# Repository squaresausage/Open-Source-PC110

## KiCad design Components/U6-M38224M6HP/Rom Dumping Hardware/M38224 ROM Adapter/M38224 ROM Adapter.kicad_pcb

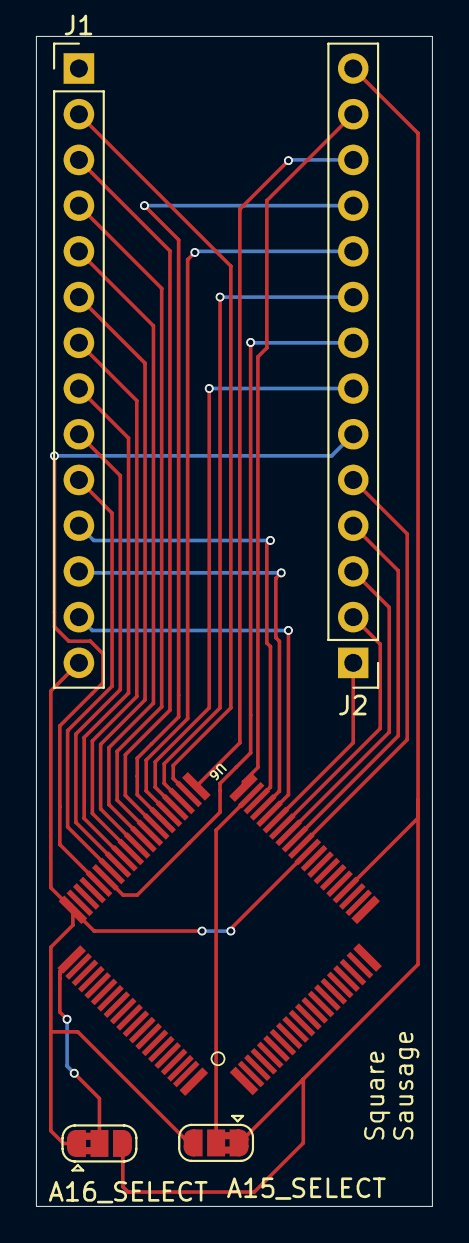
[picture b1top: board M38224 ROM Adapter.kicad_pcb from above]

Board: 2 copper layers, 22.0 x 65.0 mm, 5 parts (0 on the bottom side), 29 nets.

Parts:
J1, J2: Conn_01x14; PinHeader_1x14_P2.54mm_Vertical
JP1: A15_SELECT; SolderJumper-3_P1.3mm_Bridged2Bar12_RoundedPad1.0x1.5mm
JP2: A16_SELECT; SolderJumper-3_P1.3mm_Bridged2Bar12_RoundedPad1.0x1.5mm
U6: M38223E4HP; QFN-80

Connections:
#CE: J2.6, U6.56 (P36)
#OE: J2.8, U6.55 (P37)
A0: J1.10, U6.54 (SEG00)
A1: J1.9, U6.53 (SEG01)
A2: J1.8, U6.52 (P02)
A3: J1.7, U6.51 (P03)
A4: J1.6, U6.50 (P04)
A5: J1.5, U6.49 (P05)
A6: J1.4, U6.48 (P06)
A7: J1.3, U6.47 (SEG07)
A8: J2.11, U6.46 (P10)
A9: J2.10, U6.45 (P11)
A10: J2.7, U6.44 (P12)
A11: J2.9, U6.43 (P13)
A12: J1.2, U6.42 (P14)
A13: J2.12, U6.41 (P15)
A14: J2.13, U6.40 (P16)
A15: JP1.2 (C), U6.39 (P17)
A16: JP2.2 (C), U6.61 (SEG9)
D0: J1.11, U6.38 (P20)
D1: J1.12, U6.37 (P21)
D2: J1.13, U6.36 (P22)
D3: J2.1, U6.35 (P23)
D4: J2.2, U6.34 (P24)
D5: J2.3, U6.33 (P25)
D6: J2.4, U6.32 (P26)
D7: J2.5, U6.31 (P27)
GND: J1.14, JP1.3 (B), JP2.1 (A), U6.30 (GND), U6.60 (SEG10)
VCC: J2.14, JP1.1 (A), JP2.3 (B), U6.24 (P40)

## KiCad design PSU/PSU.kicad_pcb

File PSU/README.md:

## Here is the PCB Layout for the PSU board

Layer Stack-up

| Index | Layer name | Description  |
| ----- | ---------- | ------------ |
| 1     | FC         | Top          |
| 2     | IC         | Signal       |
| 3     | IP         | Ground       |
| 4     | BC         | Bottom       |

Here is a render of FC, IC, IP and BC:

Here are 3D models of the PSU board:

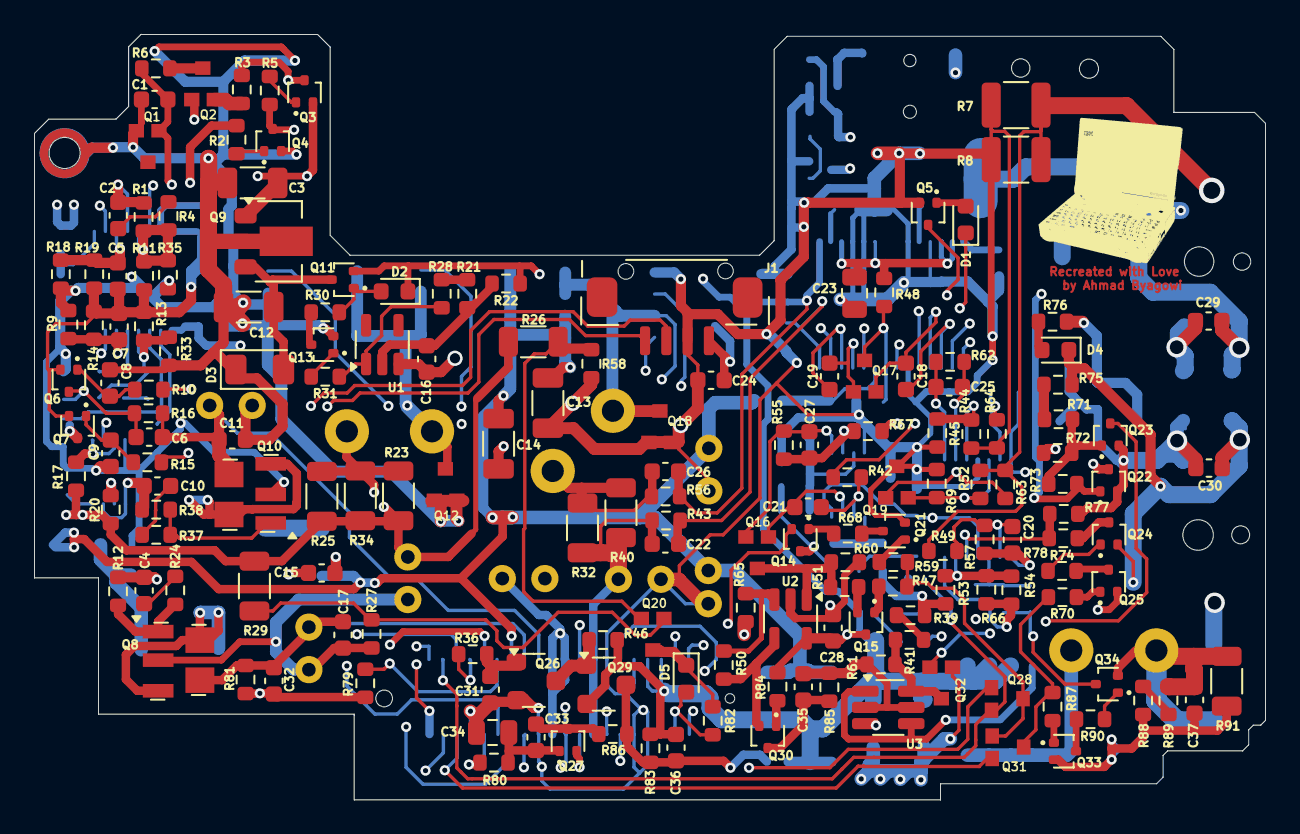
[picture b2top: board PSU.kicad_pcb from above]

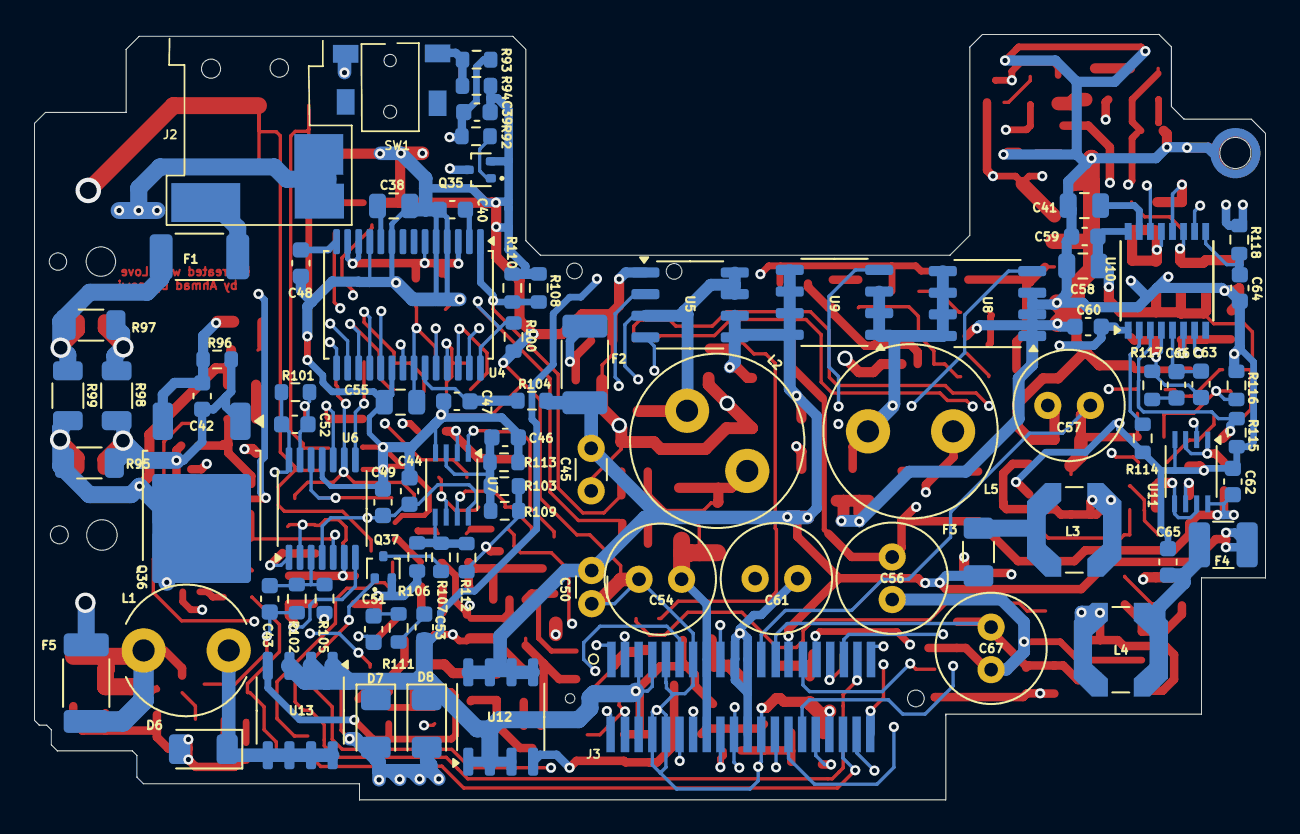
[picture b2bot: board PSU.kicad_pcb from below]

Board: 4 copper layers, 72.3 x 45.0 mm, 257 parts (86 on the bottom side), 155 nets.

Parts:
C1, C5, C7, C16, C24, C28, C36, C46, C47, C59: 150nF; C_0603_1608Metric
C2: 4.7nF; C_0603_1608Metric
C3: 5.2uF; C_1206_3216Metric
C4: 2.5nF; C_0603_1608Metric
C6, C20: 100pF; C_0603_1608Metric
C8, C33: 24nF; C_0603_1608Metric
C9, C17, C22, C26, C29, C30, C32, C39, C40, C48: 10nF; C_0603_1608Metric
C10: 3.6nF; C_0603_1608Metric
C11, C15, C37, C44, C49: 180nF; C_0603_1608Metric
C12: 1.2uF; C_1206_3216Metric
C13, C14: 1.5uF; C_1206_3216Metric
C18, C42, C51, C53, C64: 120nF; C_0603_1608Metric
C19: 18nF; C_0603_1608Metric
C21: 12nF; C_0603_1608Metric
C23, C34, C38, C41, C55, C58: 1.5uF; C_0805_2012Metric
C25, C27, C31, C35, C66: 1.2nF; C_0603_1608Metric
C43: 10pF; C_0603_1608Metric
C45: 33uF 20V; C_Disc_D3.0mm_W1.6mm_P2.50mm
C50: 56uF 25V EC; EC
C52, C60: 1nF; C_0603_1608Metric
C54, C61: 47uF 6.3v; C_Radial_D6.3mm_H11.0mm_P2.50mm
C56: 47uF 6.3V; C_Radial_D6.3mm_H11.0mm_P2.50mm
C57: 15uF 16V; C_Radial_D6.3mm_H11.0mm_P2.50mm
C62, C65: 100nF; C_0603_1608Metric
C63: 5.1nF; C_0603_1608Metric
C67: 18uF 50V; C_Radial_D6.3mm_H11.0mm_P2.50mm
D1: 8-2; D_0603_1608Metric
D2: 5-9; D_0603_1608Metric
D3, D6: DNP; D_1206_3216Metric
D4: 18; D_0603_1608Metric
D5: 3^9; D_0603_1608Metric
D7, D8: s.3 4F; D_1206_3216Metric
F1, F5: 2.5A; Fuse_2010_5025Metric
F2: 830mA; Fuse_2010_5025Metric
F3: 15; Fuse_1206_3216Metric
F4: 10; Fuse_1210_3225Metric
J1: Backllight_Connector
J2: PSU_Jack
J3: PSU_Connector_Receptor
L1: 10uH; L_Radial_D7.5mm_P5.00mm_Fastron_07P
L2, L5: 10uH; L_Radial_D10.0mm_P5.00mm_Fastron_07M
L3: 68uH; L_Coilcraft_LPS5030
L4: 470uH; L_Coilcraft_LPS5030
Q1: R4C; 3D
Q2, Q32: K; 3D
Q3, Q6, Q7, Q11, Q14, Q24, Q34: 6LS; SOT-416
Q4, Q13, Q15, Q33, Q37: 8LR; SOT-416
Q5, Q21, Q22, Q23, Q27, Q30, Q35: 8C; SOT-416
Q8: 303 5H; SOT-powerT
Q9: KD 3.E; SOT-89-3
Q10: 103 5G; SOT-powerT
Q12, Q18: Q; 3D
Q16, Q17, Q19: M2P; 3D
Q20, Q28, Q31: W6; 3D
Q25: 8LB; SOT-416
Q26: G16; SOT-23-PC110
Q29: H15; SOT-23-PC110
Q36: 3P4J; TO-252-2
R1, R50, R66, R82, R108: DNP; R_0603_1608Metric
R2, R10, R21, R31, R70, R74, R83, R87, R90: 470k; R_0603_1608Metric
R3, R36, R65, R71, R72, R75, R76, R93: 1k; R_0603_1608Metric
R4, R11, R13, R17, R19, R20, R30, R33, R35, R44, R52, R61, R63, R64, R85, R86, R103, R114, R117: 10k; R_0603_1608Metric
R5, R15, R22, R54, R57, R59, R77, R80, R84, R92, R105: 100k; R_0603_1608Metric
R6, R38: 470; R_0603_1608Metric
R7, R8: 0.1; R_1210_3225Metric
R9, R18, R112, R113: 20k; R_0603_1608Metric
R12: 2.2k; R_0603_1608Metric
R14: 12k; R_0603_1608Metric
R16: 130k; R_0603_1608Metric
R23, R25, R32, R34: 0.1; R_1206_3216Metric
R24: 220; R_0603_1608Metric
R26: 103 (RT1); R_1206_3216Metric
R27, R39, R41, R51, R58, R60, R106: 4.7k; R_0603_1608Metric
R28: 0; R_0603_1608Metric
R29: 103 (RT2); R_1206_3216Metric
R37: 120; R_0603_1608Metric
R40: 0.22; R_1206_3216Metric
R42, R47, R67, R68, R73, R79, R94: 47k; R_0603_1608Metric
R43, R56: 300; R_0603_1608Metric
R45, R62, R69, R81, R101, R109: 200k; R_0603_1608Metric
R46, R55, R88, R89: 1M; R_0603_1608Metric
R48, R104, R118: 100; R_0603_1608Metric
R49, R53, R78, R102: 300k; R_0603_1608Metric
R91, R95, R97: DNP; R_1206_3216Metric
R96: 1.8k; R_0603_1608Metric
R98, R99: 0; R_1206_3216Metric
R100, R110: 7.5k; R_0603_1608Metric
R107: 2k; R_0603_1608Metric
R111: 33; R_0603_1608Metric
R115: 11K; R_0603_1608Metric
R116: 15k; R_0603_1608Metric
SW1: PSU-SW1
U1: D9D; SOT-23-5
U2: TA; SOT-23-5
U3: 6.5 5F; SOT-23-6_Handsoldering
U4: MAX786CAI; TSSOP-28_6.1x9.7mm_P0.65mm
U5: K2337; SOP-8_3.9x4.9mm_P1.27mm
U6: 7064; TSSOP-14_4.4x5mm_P0.65mm
U7: 5W01; SSOP-8-PSU
U8, U9: 2556; SOP-8_3.9x4.9mm_P1.27mm
U10: 9742; SSOP-16_4.4x5.2mm_P0.65mm
U11: 7W14; SSOP-8-PSU
U12, U13: J421; SOP-8_3.9x4.9mm_P1.27mm

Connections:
BATT_POS: R7.2, R8.2, R49.1, R52.2, R63.2
C1_1: C2.1, R4.1
C1_2: C2.2, R1.1, U10.12
C6_1: C4.1, R24.2
C6_2: C4.2, R12.2, U11.2
C8_1: C7.1, R9.2, R14.2, U10.6
C14_2: C12.2, D3.2, Q9.3, Q11.3
C31_1: C33.1, Q27.3, R86.2
C32_1: C33.2, C34.1, Q27.1, R80.1
C33_1: C31.1, Q26.1, R36.1
C35_2: C36.2, Q29.3, R83.2, R86.1, U12.4
C36_1: C35.1, R61.1, R85.2, U3.2, U3.5
C36_2: C35.2, Q30.3, R85.1
D1_2: D1.2, Q5.1
D2_3_PC110: J3.26, Q23.3
D18_2_3_PC110: J1.1, J3.40
D28_1_PC110: C6.2, C11.1, C57.1, J3.12, Q10.4, R16.2
F3_1: F3.1, L3.1
F65_ENAVEE_PC110: J3.35, R15.1
GND: C1.1, C3.1, C8.2, C9.1, C11.2, C12.1, C13.2, C14.2, C15.2, C16.2, C17.1, C23.1, C24.1, C28.1, C30.1, C31.2, C34.2, C37.1, C38.2, C39.2, C40.1, C41.1, C42.2, C44.2, C45.1, C46.2, C47.1, C48.2, C49.2, C50.1, C51.1, C54.2, C55.1, C56.1, C57.2, C58.1, C59.2, C60.1, C61.2, C62.1, C64.2, C65.2, C67.1, D3.1, D6.2, J1.3, J3.5, J3.7, J3.9, J3.24, J3.25, J3.29, J3.32, J3.37, Q1.1, Q4.2, Q5.2, Q8.2, Q9.2, Q10.2, Q12.1, Q12.3, Q13.2, Q18.1, Q18.3, Q19.2, Q21.2, Q22.2, Q23.2, Q25.2, Q26.2, Q27.2, Q33.2, Q35.2, Q36.1, Q37.2, R7.1, R8.1, R9.1, R18.2, R27.1, R33.2, R35.2, R39.2, R44.1, R45.1, R53.1, R58.1, R60.2, R64.1, R69.2, R72.1, R77.2, R88.1, R91.1, R94.2, R95.2, R96.2, R98.2, R100.2, R105.2, R106.2, R108.1, R110.1, R113.2, R114.2, R115.2, R116.1, U1.3, U2.2, U3.3, U4.4, U4.5, U4.9, U4.11, U4.20, U5.1, U6.11, U7.4, U8.1, U8.2, U8.3, U11.4
J1_2: J1.2, J3.20
J1_4: C24.2, F2.1, J1.4
J5_6_PC110: D1.1, J3.6, Q32.1
J5_33_PC110: C39.1, J3.33, R92.1, R93.2
JRC_IN1+: C43.1, R102.1, R105.1, U6.3
JRC_IN1-: C20.2, R49.2, R57.2, U6.2
JRC_IN2+: R77.1, R78.1, U6.5
JRC_IN2-: R53.2, R54.2, R66.2, U6.6
JRC_IN3+: R44.2, R45.2, U6.10
JRC_IN3-: C25.2, Q19.3, R62.2, R63.1, U6.9
JRC_IN4+: Q19.1, R52.1, R69.1, U6.12
JRC_IN4-: C52.2, R64.2, R101.2, U6.13
JRC_VDD: C44.1, C49.1, Q3.3, R3.1, U6.4, U7.8
L1_2: D6.1, L1.2, U13.5, U13.6, U13.7, U13.8
L2_2: L3.2, Q10.3, Q10.5
M38_P20_PC110: J3.19, Q28.1, Q37.1
M38_P21_PC110: J3.39, Q28.3
M38_P52_PC110: J3.18, R2.1
M38_P53_PC110: J3.38, Q31.1
M38_P60_PC110: C25.1, J3.1, R62.1, U6.8
M38_P61_PC110: C52.1, J3.2, R42.1, R101.1, U6.14
M38_P63_PC110: C20.1, J3.21, R57.1, R67.2, U6.1
M38_P64_PC110: J3.27, R54.1, R66.1, U6.7
M38_VREF_PC110: C1.2, J3.30, Q1.3, Q14.2, R6.1
MAX_BST3: C19.2, Q17.3, U4.25
MAX_BST5: C18.2, Q17.1, U4.18
MAX_CS3: C26.2, R56.2, R108.2, R110.2, U4.1
MAX_CS5: L5.1, R23.2, R25.2, R34.2, U4.15
MAX_DH3: U4.27, U5.4
MAX_DH5: U4.16, U9.4
MAX_DL3: U4.24, U5.2
MAX_DL5: U4.19, U8.4
MAX_FB3: C22.2, R43.2, R100.1, U4.28
MAX_LX3: C19.1, L2.1, Q18.2, U4.26, U5.3, U5.7, U5.8
MAX_LX5: C18.1, L5.2, Q12.2, U4.17, U8.5, U8.6, U8.7, U8.8, U9.1, U9.2, U9.3
MAX_REF: C38.1, U4.10
MAX_SS3: C40.2, U4.2
MAX_SS5: C48.1, U4.14
MAX_VL: C55.2, Q17.2, R48.1, U4.22
MAX_VL+: C47.2, R104.1, U4.23
ON3_ON5_VH_SHDN#: C23.2, R48.2, U4.3, U4.6, U4.12, U4.13
PNET1_PC110: C22.1, C54.1, J3.8, J3.28, R32.1, R40.1, R43.1
PNET4_PC110: C36.1, C53.2, D2.1, D7.1, D8.1, J3.3, J3.4, J3.23, Q11.2, Q29.2, R22.2, R46.2, R83.1, U12.1, U12.2, U12.3, U13.1, U13.2, U13.3
PNET5_PC110: C28.2, C56.2, C61.1, C62.2, J3.10, J3.11, J3.31, Q2.3, Q15.3, R17.2, R20.2, R23.1, R25.1, R26.1, R29.2, R34.1, R84.2, R118.1, U2.5, U4.21, U11.8
PWR_IN_10v5: C30.2, D4.1, D7.2, D8.2, Q24.2, Q32.3, Q36.2, R75.2, R95.1, R99.2
PWR_IN_NEG: C29.1, J2.2, J2.3, R97.2, R98.1
PWR_IN_POS: F1.2, J2.1
PWR_IN_POS_Fuse: C29.2, F1.1, R97.1, R99.1
Q3_1: Q4.1, R2.2
Q3_3: Q4.3, Q5.3, Q22.3, R5.2
Q4_1: Q3.1, R5.1
Q6_2: C5.1, C7.2, C58.2, C59.1, Q6.2, Q7.2, R11.2, R13.1, R14.1, R19.2, U10.16
Q7_1: C8.1, Q6.1, R10.1
Q7_3: C6.1, Q6.3, R16.1, R116.2, U10.14
Q8_1: Q8.1, R12.1, R24.1
Q8_5: L4.1, Q8.3, Q8.5
Q9_1: Q10.1, R37.1, R38.1
Q13_3: Q13.3, R30.1
Q14_2: D5.1, Q20.2, R82.1
Q20_1: C27.2, Q16.1, R55.2, U7.1
Q22_1: Q24.1, R74.1
Q27_3: Q26.3, Q29.1, R46.1
Q29_2: Q31.2, R70.1, R87.2
Q30_2: Q28.2, Q31.3, R47.2, R59.2
Q33_2: C37.2, F5.2, L1.1, Q34.2, R89.2, R91.2
Q33_3: C43.2, Q34.3, R102.2
Q36_3: Q37.3, R107.2
Q43_2_PC110: C17.2, C32.2, C67.2, J3.13, Q8.4, R81.2
Q49_1_PC110: D5.2, J3.22, R82.2
R2_2: Q2.1, R3.2
R6_2: Q2.2, R6.2
R11_1: R20.1, U10.7, U11.6
R17_2: C9.2, Q7.1, R15.2
R19_1: R17.1, U10.10, U11.1, U11.3
R20_1: C5.2, R18.1, R19.1, U10.11
R21_1: Q13.1, R31.1
R21_2: R28.1, R31.2, U1.1
R24_2: C10.1, R38.2, U11.5, U11.7
R26_2: R21.2, R28.2
R31_1: C16.1, R21.1, R22.1, U1.2
R32_1: R1.2, R4.2, R11.1, R35.1, U10.13
R35_2: D2.2, Q11.1, R30.2
R36_1: C63.2, R13.2, R33.1, R117.1, U10.4
R36_2: C10.2, R37.2
R38_1: Q20.3, R27.2, R29.1
R48_2: Q20.1, R26.2, R58.2
R50_1: Q30.2, R50.1, U2.4
R50_2: R50.2, R65.2, U2.3
R51_1: Q16.2, R51.1, R60.1, U2.1
R51_2: Q15.2, R51.2
R54_2: R39.1, R41.2
R56_1: C26.1, L2.2, R32.2, R40.2, R56.1
R59_1: Q21.1, R59.1
R61_1: Q15.1, R47.1
R68_1: Q14.1, R68.1
R68_2: Q21.3, R68.2
R70_2: Q25.3, R74.2
R72_1: D4.2, R76.1
R72_2: C42.1, Q36.3, R76.2, R96.1
R73_2: Q25.1, R70.2
R73_2_PC110: J3.15, R79.2
R76_1: R71.1, R75.1
R77_1: Q23.1, R71.2, R72.2, R73.1
R77_2: Q22.1, Q35.3, R73.2
R78_2: Q24.3, R78.2
R80_1: C32.1, Q7.3, R79.1, R81.1, R115.1, U10.3
R82_1: Q30.1, R84.1
R88_1: Q33.1, R87.1
R89_1: R88.2, R89.1
R91_1: Q33.3, R90.1
R91_2: Q34.1, R90.2
R92_2: Q35.1, R92.2
R104_1: R106.1, R107.1, R112.1, U7.5
R106_1: C51.2, R111.1
R106_2: C53.1, R111.2
R111_2: Q14.3, R103.2, R109.2, R112.2
R111_!: C46.1, R103.1, R109.1, R113.1, U7.3
R115_2: C66.2, R117.2
R284_2_PC110: C13.1, C14.1, C45.2, C50.2, F2.2, F3.2, F4.2, J3.14, R104.2, U5.5, U5.6, U9.5, U9.6, U9.7, U9.8, U12.5, U12.6, U12.7, U12.8
R284_2_PC110_Fuse: C65.1, F4.1, L4.2
SW1_2: R93.1, R94.1, SW1.2
U3_1: U3.1, U3.4, U13.4
U3_6: Q32.2, R41.1, R61.2, U3.6
U6_2: C27.1, R55.1, R67.1, U7.2
U6_6: C21.1, R42.2, U7.6
U6_7: C21.2, Q16.3, U7.7
U11_1: C60.2, R65.1, U10.1
U11_2: R114.1, U10.2
U11_5: C63.1, C66.1, U10.5
U11_9: C64.1, R118.2, U10.9
U11_15: C41.2, U10.15
U21_131_PC110: J3.34, R10.2
U54_1D_PC110: J3.17, R36.2
U54_1Q_PC110: J3.36, R80.2
U54_VCC_PC110: C3.2, J3.16, Q3.2, Q9.1, SW1.1
